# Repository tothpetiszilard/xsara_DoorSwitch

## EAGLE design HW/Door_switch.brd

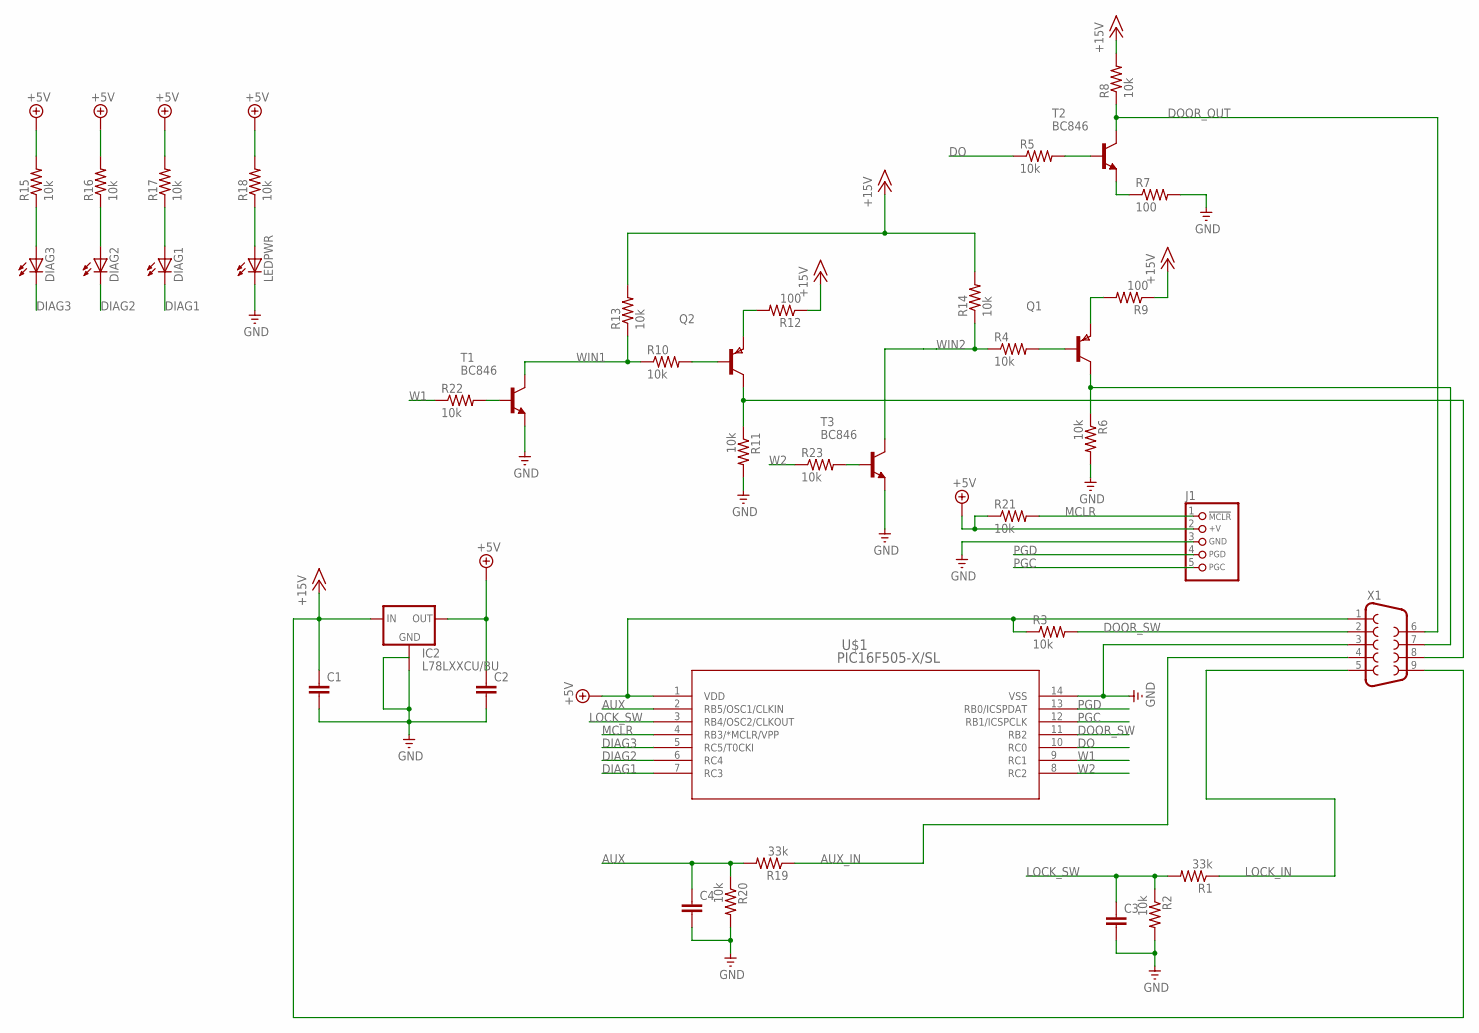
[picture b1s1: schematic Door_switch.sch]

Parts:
C1, C2, C3, C4: CC1206; C1206
DIAG1, DIAG2, DIAG3: LEDCHIP-LED0603; CHIP-LED0603
IC2: L78LXXCU/BU; SOT89
J1: CON_HEADER_PRG_PIC_ICSPA; HEADER_PRG_1X05
LEDPWR: LEDCHIP-LED0603; CHIP-LED0603
Q1, Q2: PNPSOT23; SOT-23
R1, R19: 33k; 0603-RES
R2, R3, R4, R5, R6, R8, R10, R11, R13, R14, R15, R16, R17, R18, R20, R21, R22, R23: 10k; 0603-RES
R7, R9, R12: 100; 0603-RES
T1, T2, T3: BC846; SOT23
U$1: PIC16F505-X/SL; SOIC14-N_MC
X1: F09HP

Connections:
+5V: C2.1, IC2.1 (OUT), J1.2 (+V), R3.1, R15.2, R16.2, R17.2, R18.2, R21.1, U$1.1 (VDD), X1.1
+15V: C1.1, IC2.3 (IN), R8.2, R9.1, R12.1, R13.2, R14.2, X1.9
AUX: C4.1, R19.2, R20.1, U$1.2 (RB5/OSC1/CLKIN)
AUX_IN: R19.1, X1.4
DIAG1: DIAG1.C, U$1.7 (RC3)
DIAG2: DIAG2.C, U$1.6 (RC4)
DIAG3: DIAG3.C, U$1.5 (RC5/T0CKI)
DO: R5.1, U$1.10 (RC0)
DOOR_OUT: R8.1, T2.3 (C), X1.6
DOOR_SW: R3.2, U$1.11 (RB2), X1.2
GND: C1.2, C2.2, C3.2, C4.2, IC2.2 (GND), IC2.4 (GND1), J1.3 (GND), LEDPWR.C, R2.2, R6.2, R7.2, R11.2, R20.2, T1.2 (E), T3.2 (E), U$1.14 (VSS), X1.3
LOCK_IN: R1.1, X1.5
LOCK_SW: C3.1, R1.2, R2.1, U$1.3 (RB4/OSC2/CLKOUT)
MCLR: J1.1 (/MCLR), R21.2, U$1.4 (RB3/*MCLR/VPP)
unnamed: Q2.3 (B), R10.2
unnamed: Q2.1 (C), R11.1, X1.8
unnamed: R7.1, T2.2 (E)
unnamed: R5.2, T2.1 (B)
unnamed: Q2.2 (E), R12.2
unnamed: DIAG3.A, R15.1
unnamed: DIAG2.A, R16.1
unnamed: Q1.3 (B), R4.2
unnamed: Q1.1 (C), R6.1, X1.7
unnamed: Q1.2 (E), R9.2
unnamed: DIAG1.A, R17.1
unnamed: LEDPWR.A, R18.1
unnamed: R22.2, T1.1 (B)
unnamed: R23.2, T3.1 (B)
PGC: J1.5 (PGC), U$1.12 (RB1/ICSPCLK)
PGD: J1.4 (PGD), U$1.13 (RB0/ICSPDAT)
W1: R22.1, U$1.9 (RC1)
W2: R23.1, U$1.8 (RC2)
WIN1: R10.1, R13.1, T1.3 (C)
WIN2: R4.1, R14.1, T3.3 (C)

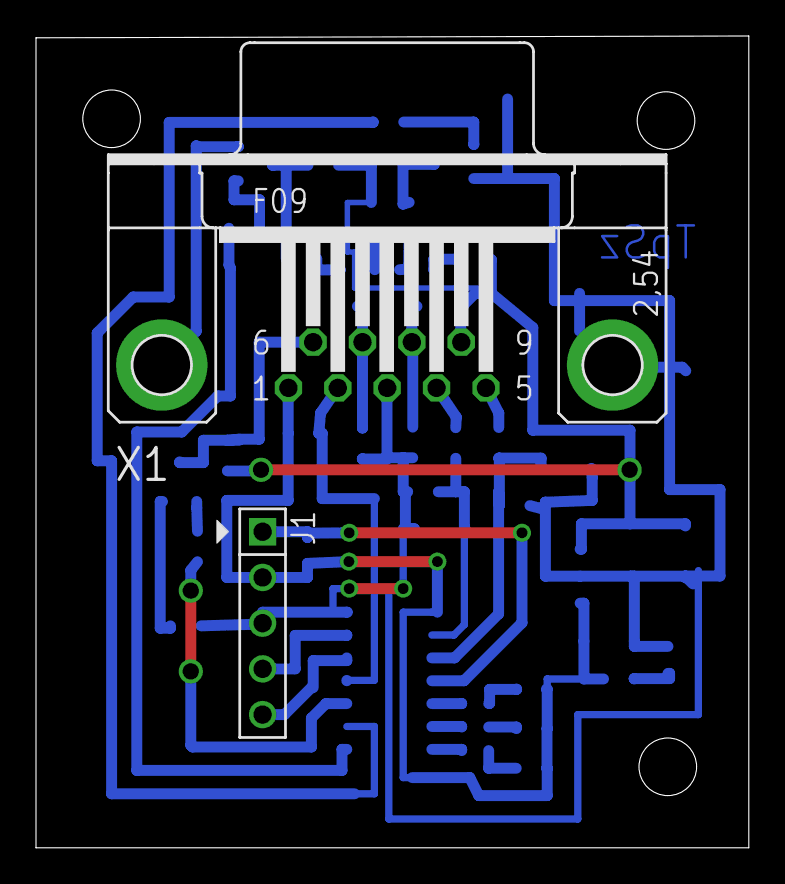
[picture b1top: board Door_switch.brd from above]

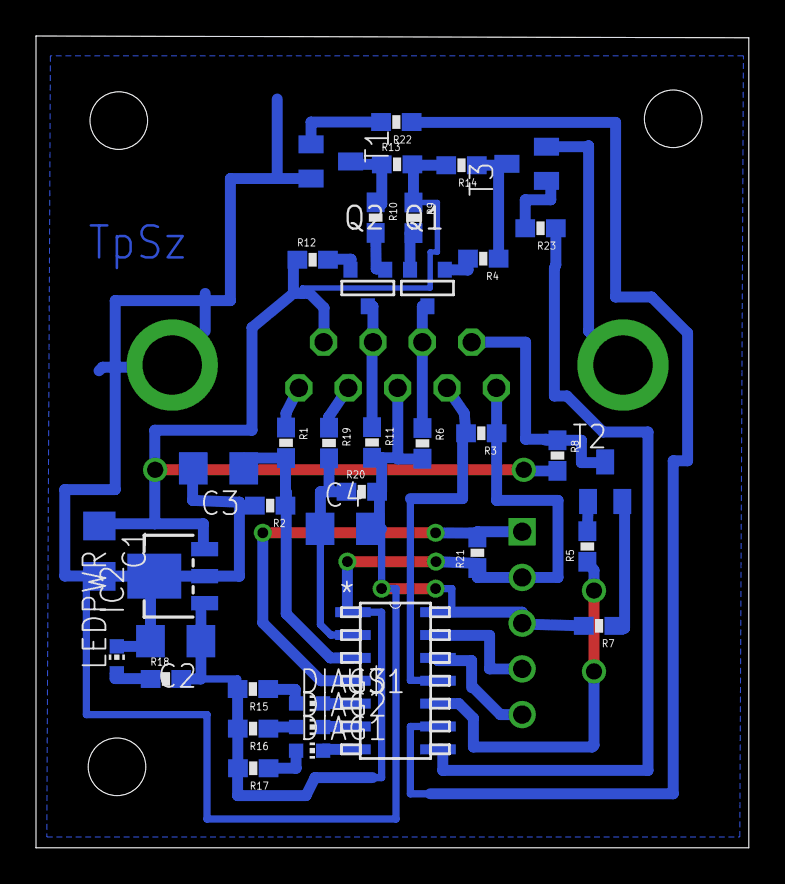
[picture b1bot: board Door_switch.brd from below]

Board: 2 copper layers, 39.6 x 45.1 mm, 40 parts (38 on the bottom side), 34 nets.

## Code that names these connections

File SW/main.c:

/*
 * File:   main.c
 * Author: tothpetiszilard
 *
 * Created on 2016. december 23., 15:12
 */

// PIC16F506 Configuration Bit Settings

// CONFIG
#pragma config OSC = IntRC_RB4EN// Oscillator Selection bits (INTRC With RB4 and 1.125 ms DRT)
#pragma config WDT = OFF        // Watchdog Timer Enable bit (WDT disabled)
#pragma config CP = OFF         // Code Protect (Code protection off)
#pragma config MCLRE = OFF      // Master Clear Enable bit (RB3/MCLR pin functions as RB3, MCLR tied internally to VDD)
#pragma config IOSCFS = ON      // Internal Oscillator Frequency Select bit (8 MHz INTOSC Speed)

// #pragma config statements should precede project file includes.
// Use project enums instead of #define for ON and OFF.

#include <xc.h>

typedef enum CAR_EN
{
    UNLOCKED_OPEN = 0U,
    UNLOCKED_CLOSED = 1U,
    LOCKED_CLOSED = 2U,
    CLOSING_WINDOWS = 3U
}car_state_t;

#define DOOR_SEN    PORTBbits.RB2
#define LOCK_SEN    PORTBbits.RB4
#define AUX_SEN     PORTBbits.RB5


#define DOOR_OUT    PORTCbits.RC0
#define WINDOW1     PORTCbits.RC1
#define WINDOW2     PORTCbits.RC2
#define LED1        PORTCbits.RC3
#define LED2        PORTCbits.RC4
#define LED3        PORTCbits.RC5

#define WINDOWS_MULTIPLIER (2U)
#define WINDOWS_DELAY 65535U

car_state_t car_status;

unsigned int windows_timer;
unsigned char windows_cnt;

void main(void) 
{
    TRISC = 0x00;
    ADCON0 = 0x00;
    TRISB = 0xFF;
    LED1 = 1;
    LED2 = 1;
    LED3 = 1;
    DOOR_OUT = 1;
    LED1 = 0;
    car_status = UNLOCKED_OPEN;
    windows_timer = WINDOWS_DELAY;
    windows_cnt = WINDOWS_MULTIPLIER;
    unsigned char door_u8;
    unsigned char lock_u8;
    while (1)
    {
        door_u8 = DOOR_SEN;
        lock_u8 = LOCK_SEN; 
        
        switch(car_status)
        {
            case UNLOCKED_OPEN:
            {
                if ((0 == door_u8) && (0 == lock_u8)) // Door closed and Vehicle unlocked
                {
                    DOOR_OUT = 0;
                    LED1 = 1;
                    car_status = UNLOCKED_CLOSED;
                }
                break;
            }
            case UNLOCKED_CLOSED:
            {
                if ( 0 != door_u8 ) // Door opened
                {
                    
                    DOOR_OUT = 1;
                    LED1 = 0;
                    car_status = UNLOCKED_OPEN;
                }
                else // Door closed
                {
                    if (0 != lock_u8) // Door closed and vehicle just locked
                    {
                        /* Vehicle locked, start locking process */
                        DOOR_OUT = 1; // Output for BSI
                        LED1 = 1;   // Switching off door led
                        WINDOW1 = 1; // Closing left window
                        WINDOW2 = 1; // Closing right window
                        LED2 = 0; // Turning on left window led
                        LED3 = 0; // Turning on right window
                        windows_timer = WINDOWS_DELAY; // Reloading the soft timer for windows closing function
                        windows_cnt = WINDOWS_MULTIPLIER; // Reloading the multiplier value for the soft timer
                        car_status = CLOSING_WINDOWS;
                    }
                }
                break;
            }
            case CLOSING_WINDOWS: // Vehicle locked and windows are closing right now
            {
                if ((0 != windows_timer) || (0 != windows_cnt)) // If there is more time to wait
                {
                    if (0 != windows_timer) // If timer still running
                    {
                        windows_timer--; // Decrease timer variable
                    }
                    else // If timer is null, but there is still a need to wait (multiplier)
                    {
                        windows_timer = WINDOWS_DELAY; // Reload the timer
                        windows_cnt--; // Decrease multiplier variable
                    }
                }
                else // Closing time is elapsed
                {
                    WINDOW1 = 0; // Stop window closer motor
                    WINDOW2 = 0; // Stop window closer motor
                    LED2 = 1;   // Turn off window led
                    LED3 = 1;
                    car_status = LOCKED_CLOSED; // Windows are closed, switch to locked state
                }
                /* Handling the following: unlocking the car when windows are closing */
                if (( 0 != door_u8 ) || (0 == lock_u8)) // If door is opened OR vehicle unlocked
                {
                    WINDOW1 = 0; // Stop motors
                    WINDOW2 = 0;
                    LED2 = 1;   // Switch off led
                    LED3 = 1;
                    /* Switching door output to unlocked state */
                    if ( 0 == door_u8 )
                    {
                        DOOR_OUT = 0; // Door is still closed
                        LED1 = 1;
                        car_status = UNLOCKED_CLOSED; /* Something happened, switch to unlocked state */
                    }
                    else
                    {
                        DOOR_OUT = 1; // Door is opened
                        LED1 = 0;    // Turn on door led
                        car_status = UNLOCKED_OPEN; /* Something happened, switch to unlocked state */
                    }
                }
                break;
            }
            case LOCKED_CLOSED:
            {
                if (0 == lock_u8) // Vehicle unlocked
                {
                    if ( 0 == door_u8 ) // Is the door closed?
                    {
                        DOOR_OUT = 0; // Door is still closed
                        LED1 = 1;
                        car_status = UNLOCKED_CLOSED; /* Switch to unlocked state */
                    }
                    else
                    {
                        DOOR_OUT = 1; // Door is opened
                        LED1 = 0;    // Turn on door led
                        car_status = UNLOCKED_OPEN; /* Switch to unlocked state */
                    }
                }
                break;
            }
            default:
                break;
        }
        
    }
}
